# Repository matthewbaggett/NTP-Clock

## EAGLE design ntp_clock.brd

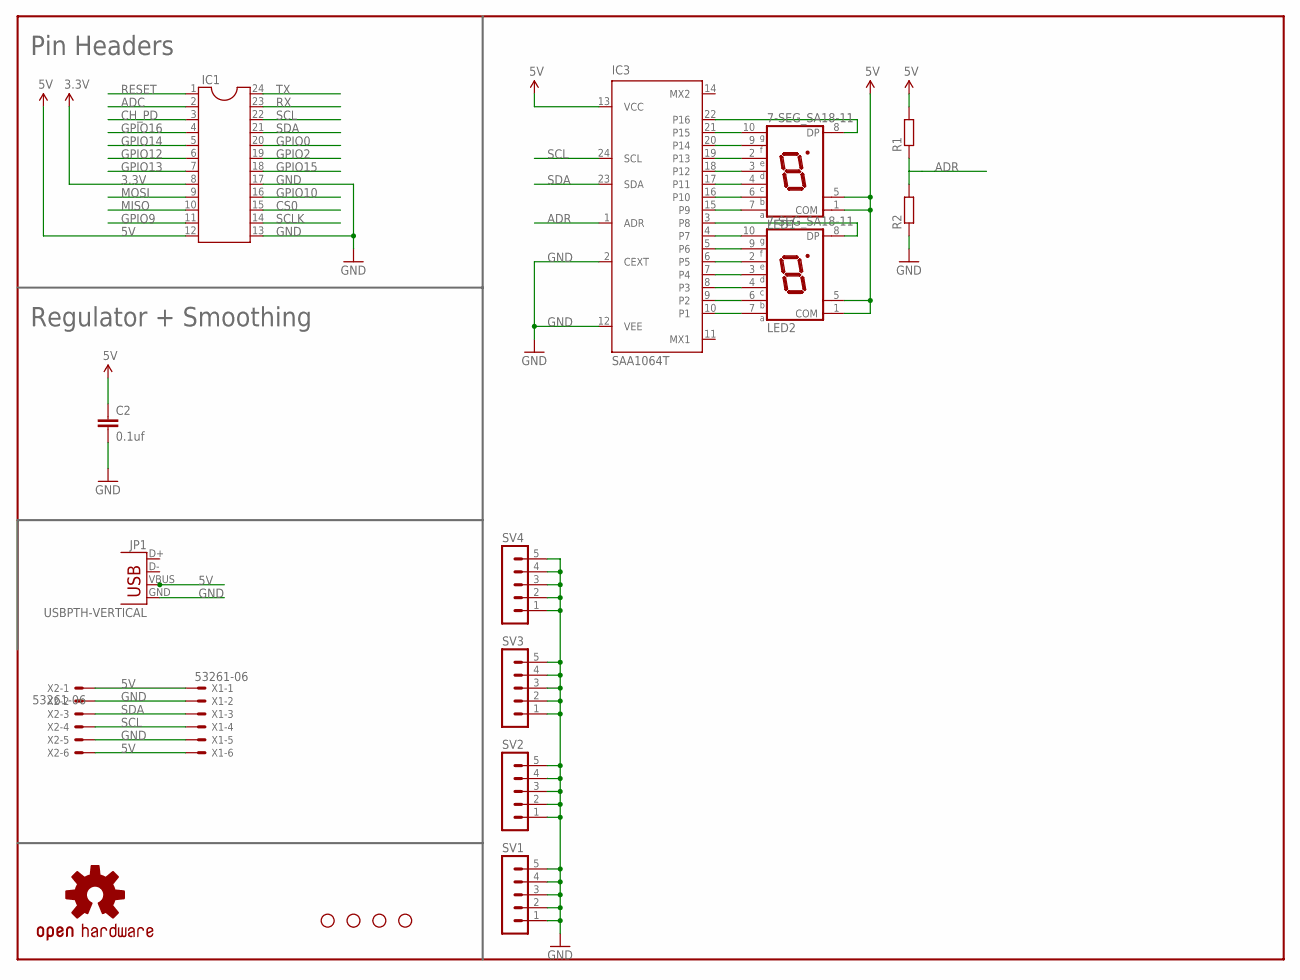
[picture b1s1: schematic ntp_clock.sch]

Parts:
C2: 0.1uf; 1206
FRAME1: FRAME-LETTERNO_PACKAGE; DUMMY
IC1: DIL24-9
IC3: SAA1064T; SO24
JP1: USBPTH-VERTICAL; USB-B-PTH-VERTICAL
LED1, LED2: 7-SEG_SA18-11; SA18-11
LOGO1: OSHW-LOGOS; OSHW-LOGO-S
R1, R2: R-EU_0207/12; 0207/12
STANDOFF1, STANDOFF2, STANDOFF3, STANDOFF4: STAND-OFF
SV1, SV2, SV3, SV4: MA05-1
X1, X2: 53261-06

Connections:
3.3V: IC1.8
5V: C2.1, IC1.12, IC3.13 (VCC), JP1.VBUS, LED1.1 (COM), LED1.5 (COM), LED2.1 (COM), LED2.5 (COM), R1.2, X1.1, X1.6, X2.1, X2.6
ADC: IC1.2
ADR: IC3.1 (ADR), R1.1, R2.2
CH_PD: IC1.3
CS0: IC1.15
GND: C2.2, IC1.13, IC1.17, IC3.2 (CEXT), IC3.12 (VEE), JP1.GND, R2.1, SV1.1, SV1.2, SV1.3, SV1.4, SV1.5, SV2.1, SV2.2, SV2.3, SV2.4, SV2.5, SV3.1, SV3.2, SV3.3, SV3.4, SV3.5, SV4.1, SV4.2, SV4.3, SV4.4, SV4.5, X1.2, X1.5, X2.2, X2.5
GPIO0: IC1.20
GPIO2: IC1.19
GPIO9: IC1.11
GPIO10: IC1.16
GPIO12: IC1.6
GPIO13: IC1.7
GPIO14: IC1.5
GPIO15: IC1.18
GPIO16: IC1.4
MISO: IC1.10
MOSI: IC1.9
unnamed: IC3.5 (P6), LED2.9 (F)
unnamed: IC3.7 (P4), LED2.3 (D)
unnamed: IC3.9 (P2), LED2.6 (B)
unnamed: IC3.10 (P1), LED2.7 (A)
unnamed: IC3.8 (P3), LED2.4 (C)
unnamed: IC3.6 (P5), LED2.2 (E)
unnamed: IC3.4 (P7), LED2.10 (G)
unnamed: IC3.3 (P8), LED2.8 (DP)
unnamed: IC3.20 (P14), LED1.9 (F)
unnamed: IC3.18 (P12), LED1.3 (D)
unnamed: IC3.16 (P10), LED1.6 (B)
unnamed: IC3.15 (P9), LED1.7 (A)
unnamed: IC3.17 (P11), LED1.4 (C)
unnamed: IC3.19 (P13), LED1.2 (E)
unnamed: IC3.21 (P15), LED1.10 (G)
unnamed: IC3.22 (P16), LED1.8 (DP)
RESET: IC1.1
RX: IC1.23
SCL: IC1.22, IC3.24 (SCL), X1.4, X2.4
SCLK: IC1.14
SDA: IC1.21, IC3.23 (SDA), X1.3, X2.3
TX: IC1.24

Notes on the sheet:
Regulator + Smoothing
Pin Headers

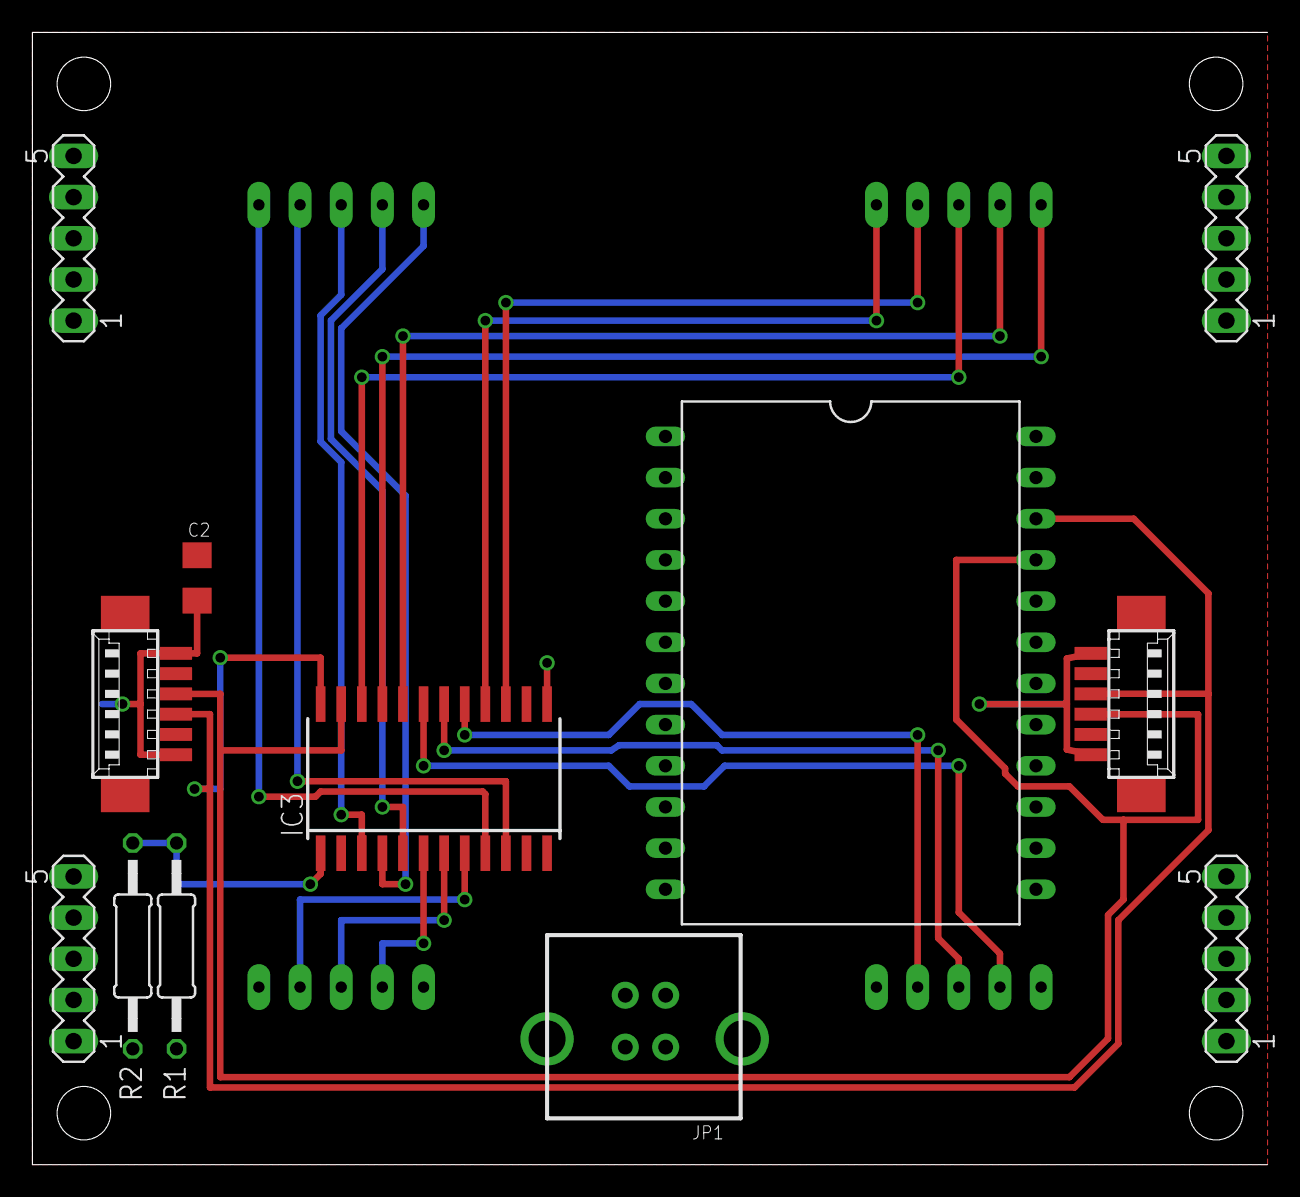
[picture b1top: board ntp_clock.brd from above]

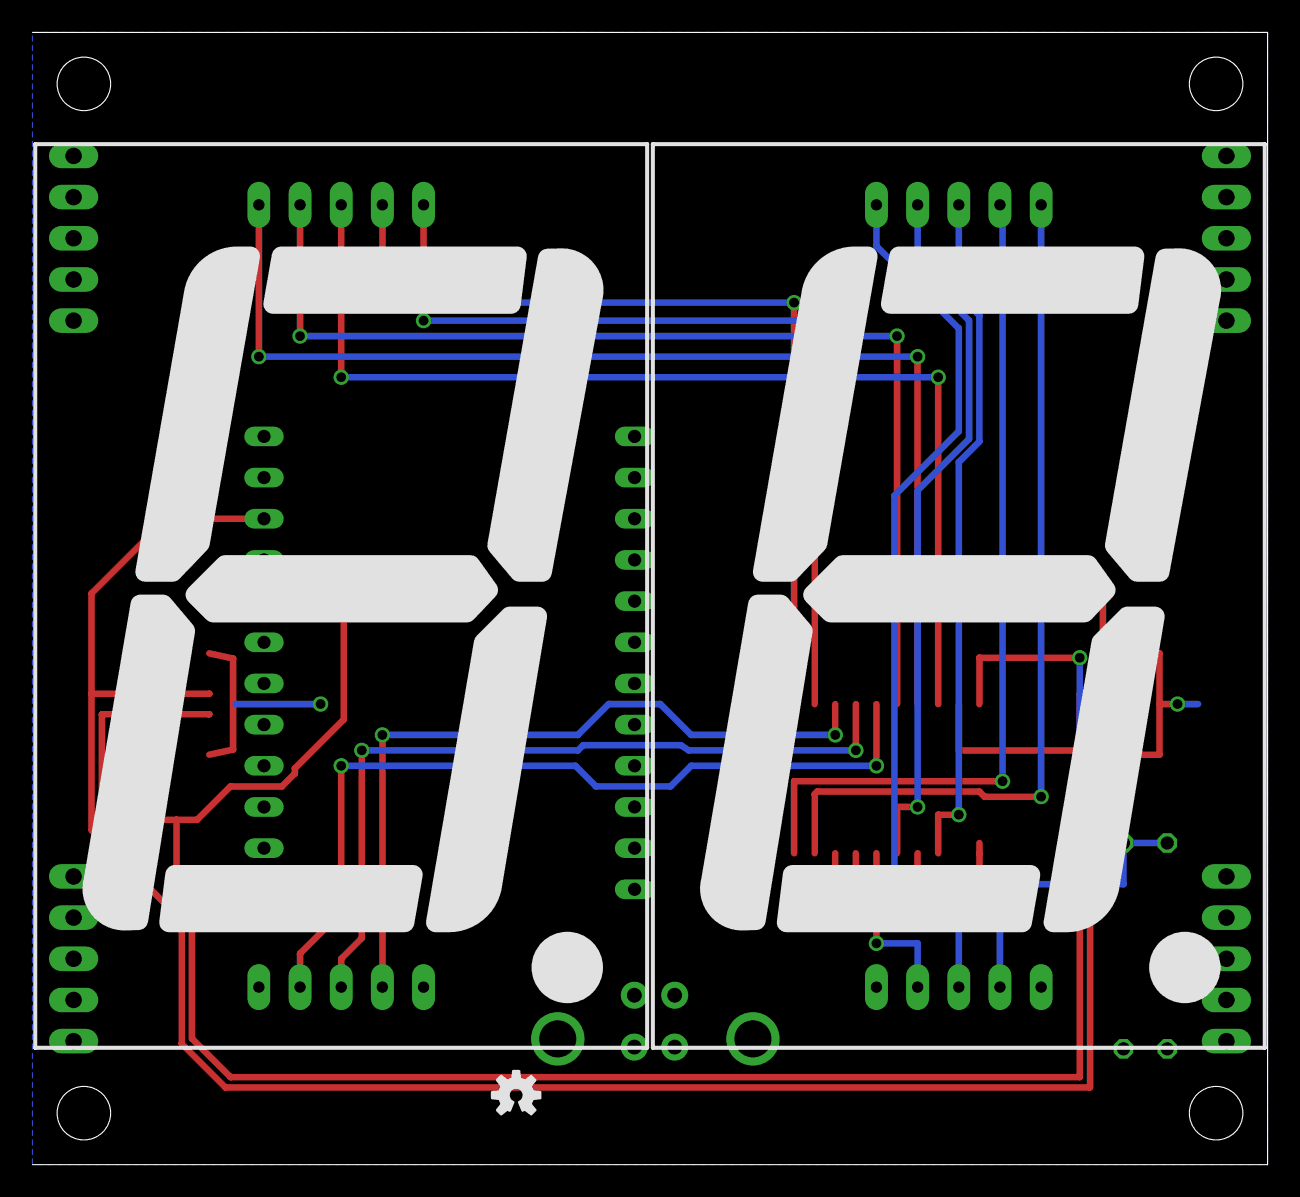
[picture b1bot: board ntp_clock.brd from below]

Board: 2 copper layers, 76.2 x 69.8 mm, 20 parts (3 on the bottom side), 21 nets.

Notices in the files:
parts and their libraries:
SparkFun-Capacitors: Licensing: Creative Commons ShareAlike 4.0 International - https://creativecommons.org/licenses/by-sa/4.0
SparkFun-Aesthetics: Released under the Creative Commons Attribution Share-Alike 4.0 License
SparkFun-Aesthetics: https://creativecommons.org/licenses/by-sa/4.0
